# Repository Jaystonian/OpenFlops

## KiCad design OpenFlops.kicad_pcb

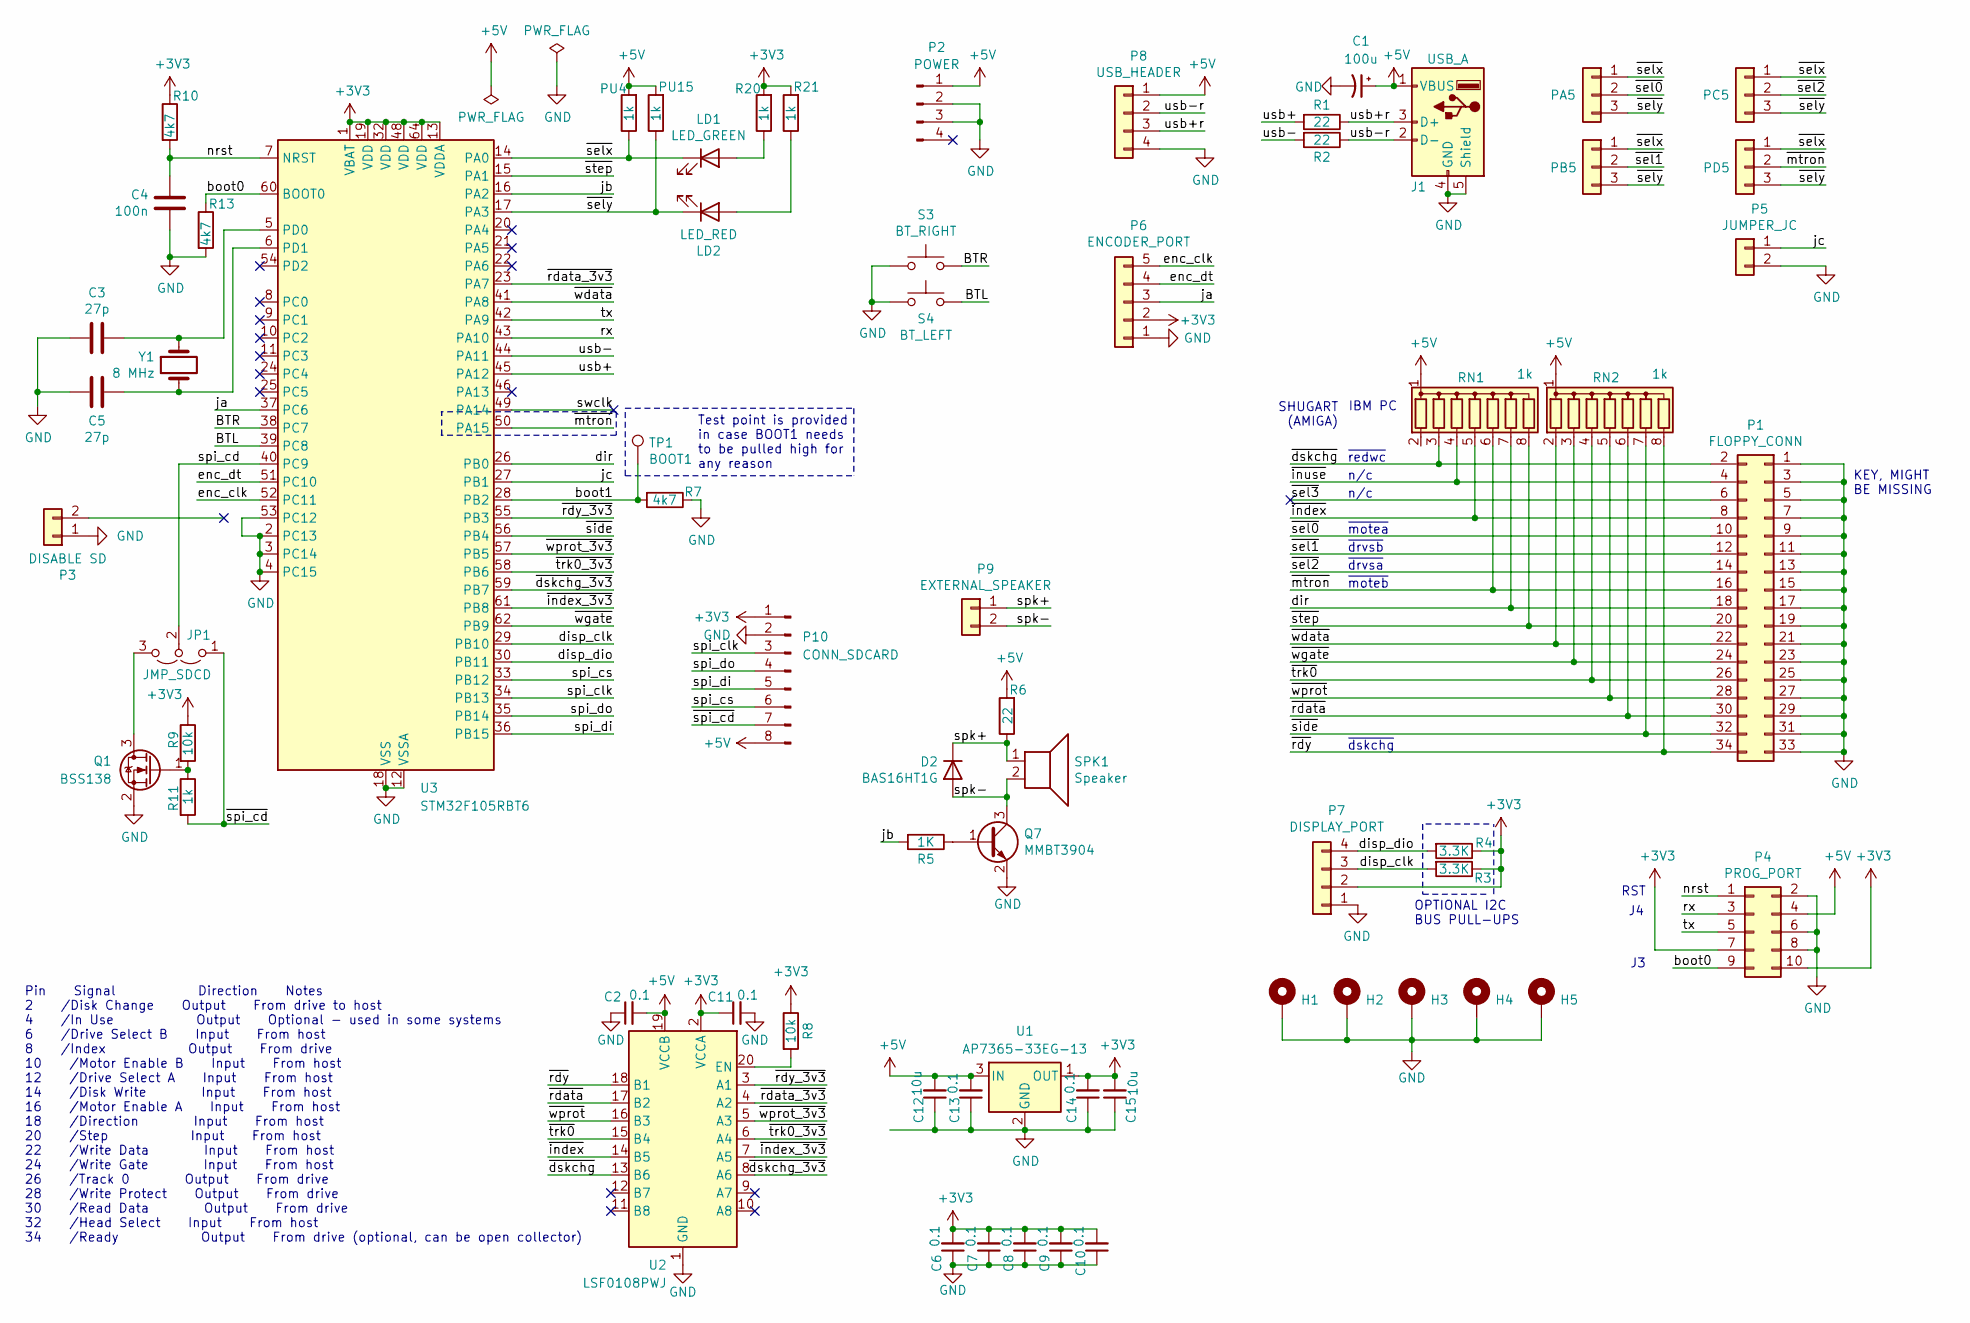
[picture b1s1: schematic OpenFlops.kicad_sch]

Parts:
C1: 100u; CP_EIA-6032-15_Kemet-U_Pad2.25x2.35mm_HandSolder
C2, C6, C7, C8, C9, C10, C11, C13, C14: 0.1; C_0805_2012Metric_Pad1.18x1.45mm_HandSolder
C3: 27p; C_0805_2012Metric_Pad1.18x1.45mm_HandSolder
C4: 100n; C_0805_2012Metric_Pad1.18x1.45mm_HandSolder
C5: 27p; C_0805_2012Metric_Pad1.18x1.45mm_HandSolder; MFG Part Num MULTILAYER CERAMIC CAPACITORS MLCC - SM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; JLCPCB PN CL21C220JBANNNC
C12, C15: 10u; C_0805_2012Metric_Pad1.18x1.45mm_HandSolder
D2: BAS16HT1G; D_SOD-323_HandSoldering
H1, H2, H3, H4, H5: MountingHole_Pad; MountingHole_3.2mm_M3_Pad_Via
J1: USB_A; USB_A_CONNFLY_DS1095-WNR0
JP1: JMP_SDCD; SolderJumper-3_P1.3mm_Open_RoundedPad1.0x1.5mm
LD1: LED_GREEN; LED_D3.0mm
LD2: LED_RED; LED_D3.0mm
P1: FLOPPY_CONN; PinHeader_2x17_P2.54mm_Vertical
P2: POWER; PinHeader_1x04_P2.54mm_Vertical
P3: DISABLE SD; PinHeader_1x02_P2.54mm_Vertical
P4: PROG_PORT; PinHeader_2x05_P2.54mm_Vertical
P5: JUMPER_JC; PinHeader_1x02_P2.54mm_Vertical
P6: ENCODER_PORT; PinHeader_1x05_P2.54mm_Vertical
P7: DISPLAY_PORT; PinHeader_1x04_P2.54mm_Vertical
P8: USB_HEADER; PinHeader_1x04_P2.54mm_Vertical
P9: EXTERNAL_SPEAKER; PinHeader_1x02_P2.54mm_Vertical
P10: CONN_SDCARD; PinHeader_1x08_P2.54mm_Vertical
PA5: Conn_01x03; PinHeader_1x03_P2.54mm_Vertical
PB5: Conn_01x03; PinHeader_1x03_P2.54mm_Vertical
PC5: Conn_01x03; PinHeader_1x03_P2.54mm_Vertical
PD5: Conn_01x03; PinHeader_1x03_P2.54mm_Vertical
PU4, PU15: 1k; R_0805_2012Metric_Pad1.20x1.40mm_HandSolder
Q1: BSS138; SOT-23_Handsoldering
Q7: MMBT3904; SOT-23_Handsoldering
R1, R2, R6: 22; R_0805_2012Metric_Pad1.20x1.40mm_HandSolder
R3, R4: 3.3K; R_0805_2012Metric_Pad1.20x1.40mm_HandSolder
R5: 1K; R_0805_2012Metric_Pad1.20x1.40mm_HandSolder
R7, R10, R13: 4k7; R_0805_2012Metric_Pad1.20x1.40mm_HandSolder
R8, R9: 10k; R_0805_2012Metric_Pad1.20x1.40mm_HandSolder
R11, R20, R21: 1k; R_0805_2012Metric_Pad1.20x1.40mm_HandSolder
RN1, RN2: 1k; R_Array_SIP8
S3: BT_RIGHT; SW_Tactile_SPST_Angled_PTS645Vx83-2LFS
S4: BT_LEFT; SW_Tactile_SPST_Angled_PTS645Vx83-2LFS
SPK1: Speaker; Buzzer_15x7.5RM7.6
TP1: BOOT1; TestPoint_Pad_D1.0mm
U1: AP7365-33EG-13; SOT-223-3_TabPin2
U2: LSF0108PWJ; TSSOP-20_4.4x6.5mm_P0.65mm
U3: STM32F105RBT6; LQFP-64_10x10mm_P0.5mm
Y1: 8 MHz; Crystal_SMD_5032-2Pin_5.0x3.2mm_HandSoldering

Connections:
+3V3: C6.2, C7.2, C8.2, C9.2, C10.2, C11.1, C14.2, C15.2, P4.7, P4.10, P6.2, P7.2, P10.1, R3.1, R4.1, R8.1, R9.1, R10.1, R20.2, R21.2, U1.1 (OUT), U2.2 (VCCA), U3.1 (VBAT), U3.13 (VDDA), U3.19 (VDD), U3.32 (VDD), U3.48 (VDD), U3.64 (VDD)
+5V: C1.1, C2.2, C12.2, C13.2, J1.1 (VBUS), P2.1, P4.4, P8.1, P10.8, PU4.2, PU15.2, R6.2, RN1.1 (common), RN2.1 (common), U1.3 (IN), U2.19 (VCCB)
/BTL: S4.2, U3.39 (PC8)
/BTR: S3.2, U3.38 (PC7)
/boot0: P4.9, R13.1, U3.60 (BOOT0)
/boot1: R7.2, TP1.1, U3.28 (PB2)
/dir: P1.18, RN1.7 (R6), U3.26 (PB0)
/disp_clk: P7.3, R3.2, U3.29 (PB10)
/disp_dio: P7.4, R4.2, U3.30 (PB11)
/enc_clk: P6.5, U3.52 (PC11)
/enc_dt: P6.4, U3.51 (PC10)
/ja: P6.3, U3.37 (PC6)
/jb: R5.2, U3.16 (PA2)
/jc: P5.1, U3.27 (PB1)
/nrst: C4.1, P4.1, R10.2, U3.7 (NRST)
/rx: P4.3, U3.43 (PA10)
/spi_cd: JP1.2 (C), U3.40 (PC9)
/spi_clk: P10.3, U3.34 (PB13)
/spi_cs: P10.6, U3.33 (PB12)
/spi_di: P10.5, U3.36 (PB15)
/spi_do: P10.4, U3.35 (PB14)
/spk+: D2.1 (K), P9.1, R6.1, SPK1.1
/spk-: D2.2 (A), P9.2, Q7.3 (C), SPK1.2
/swclk: U3.49 (PA14)
/tx: P4.5, U3.42 (PA9)
/usb+: R1.2, U3.45 (PA12)
/usb+r: J1.3 (D+), P8.3, R1.1
/usb-: R2.2, U3.44 (PA11)
/usb-r: J1.2 (D-), P8.2, R2.1
/~dskchg_3v3: U2.8 (A6), U3.59 (PB7)
/~dskchg: P1.2, RN1.3 (R2), U2.13 (B6)
/~index_3v3: U2.7 (A5), U3.61 (PB8)
/~index: P1.8, RN1.5 (R4), U2.14 (B5)
/~inuse: P1.4, RN1.4 (R3)
/~mtron: P1.16, PD5.2, RN1.6 (R5), U3.50 (PA15)
/~rdata_3v3: U2.4 (A2), U3.23 (PA7)
/~rdata: P1.30, RN2.6 (R5), U2.17 (B2)
/~rdy_3v3: U2.3 (A1), U3.55 (PB3)
/~rdy: P1.34, RN2.8 (R7), U2.18 (B1)
/~sel0: P1.10, PA5.2
/~sel1: P1.12, PB5.2
/~sel2: P1.14, PC5.2
/~sel3: P1.6
/~selx: LD1.1 (K), PA5.1, PB5.1, PC5.1, PD5.1, PU4.1, U3.14 (PA0)
/~sely: LD2.1 (K), PA5.3, PB5.3, PC5.3, PD5.3, PU15.1, U3.17 (PA3)
/~side: P1.32, RN2.7 (R6), U3.56 (PB4)
/~step: P1.20, RN1.8 (R7), U3.15 (PA1)
/~trk0_3v3: U2.6 (A4), U3.58 (PB6)
/~trk0: P1.26, RN2.4 (R3), U2.15 (B4)
/~wdata: P1.22, RN2.2 (R1), U3.41 (PA8)
/~wgate: P1.24, RN2.3 (R2), U3.62 (PB9)
/~wprot_3v3: U2.5 (A3), U3.57 (PB5)
/~wprot: P1.28, RN2.5 (R4), U2.16 (B3)
GND: C1.2, C2.1, C3.2, C4.2, C5.2, C6.1, C7.1, C8.1, C9.1, C10.1, C11.2, C12.1, C13.1, C14.1, C15.1, H1.1, H2.1, H3.1, H4.1, H5.1, J1.4 (GND), J1.5 (Shield), P1.1, P1.3, P1.5, P1.7, P1.9, P1.11, P1.13, P1.15, P1.17, P1.19, P1.21, P1.23, P1.25, P1.27, P1.29, P1.31, P1.33, P2.2, P2.3, P3.1, P4.2, P4.6, P4.8, P5.2, P6.1, P7.1, P8.4, P10.2, Q1.2 (S), Q7.2 (E), R7.1, R13.2, S3.1, S4.1, U1.2 (GND), U2.1 (GND), U3.2 (PC13), U3.3 (PC14), U3.4 (PC15), U3.12 (VSSA), U3.18 (VSS), U3.31 (VSS), U3.47 (VSS), U3.53 (PC12), U3.63 (VSS)
unnamed: JP1.1 (A), P10.7, R11.2
unnamed: JP1.3 (B), Q1.3 (D)
unnamed: LD1.2 (A), R20.1
unnamed: LD2.2 (A), R21.1
unnamed: Q1.1 (G), R9.2, R11.1
unnamed: Q7.1 (B), R5.1
unnamed: R8.2, U2.20 (EN)
unnamed: C3.1, U3.5 (PD0), Y1.1
unnamed: C5.1, U3.6 (PD1), Y1.2

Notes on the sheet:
Pin Signal Direction Notes 2 /Disk Change Output From drive to host 4 /In Use Output Optional - used in some systems 6 /Drive Select B Input From host 8 /Index Output From drive 10 /Motor Enable B Input From host 12 /Drive Select A Input From host 14 /Disk Write Input From host 16 /Motor Enable A I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
RST
~{drvsa}
~{dskchg}
SHUGART (AMIGA)
KEY, MIGHT BE MISSING
~{drvsb}
OPTIONAL I2C BUS PULL-UPS
n/c
~{redwc}
~{moteb}
IBM PC
Test point is provided in case BOOT1 needs to be pulled high for any reason
~{motea}

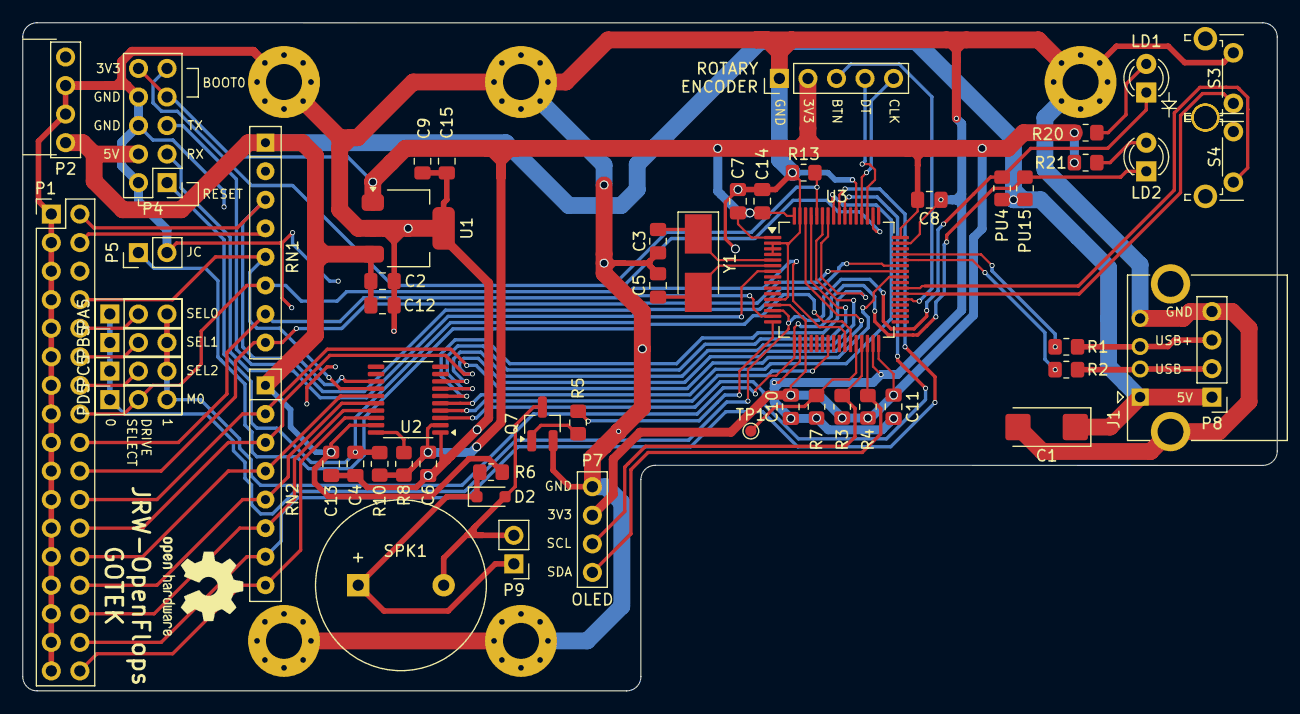
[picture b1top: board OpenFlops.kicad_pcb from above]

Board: 2 copper layers, 111.6 x 59.4 mm, 61 parts (0 on the bottom side), 53 nets.

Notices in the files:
OpenFlops.kicad_pcb:
Licensed under CERN OHL v.1.2
